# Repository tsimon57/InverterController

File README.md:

# InverterController
circuit to control MicroSolar inverter using remote cable socket
My vacation is your worst nightmare. Well, at least that is what the bumper sticker says – it’s referring to Burning Man. It’s well known that among the tens of thousands of people attending this arts festival in Nevada at the end of each Summer there are lots of high tech luminaries. I also have gone many times – not to say that I am a luminary. It’s a common tradition of so-called ‘burners’ to build complex projects to take with them that provide some of the comforts of home and more during the week of survival camping in the Black Rock Desert. Ad hoc showers, aluminum can recycling stations, elaborate cooking arrangements, alternative energy systems, coffee carts, colorful lighting setup, fire shooting vehicles, huge sound systems – pretty much anything you can think of and many you never even imagined – are brought out and assembled on the “playa.”

There is nothing for sale there – you must plan on bringing everything you need. There might be some sociable gifting, and people will probably help you out in a pinch, but start with the basics, like 2 gallons of water per person per day, and go from there. Notwithstanding, you can buy coffee and ice at what they call Center Camp. That’s it. Everything else is on you. The ice is for people’s coolers. And we are talking about 80,000 people camping in the desert heat. Of course, people bring RV’s (some consider that cheating) and others have generators and refrigerators (might also be cheating). I have relied on ice and coolers for many of my ten day stints out there. Needless to say, dealing with ice can be a major hassle. Getting very cold and heavy ice at Center Camp and bringing it back to your camp on foot or bicycle can be an ordeal. When it melts, it fills your cooler with slushy water that inevitably finds its way into your food. 

So I decided, what better project than to use solar power to run a small freezer to freeze blue ice packs? With a freezer working well enough, I can swap between two sets of blue ice packs each day. One set is getting deep frozen while the other set is keeping my Yeti cooler nice and cold. Last Summer, I started to assemble my system. It needed to be as compact as possible, weather proof, not easily damaged (either on the trip there or once set up), self-sustaining, reliable and reasonably priced. 

I ruled out an off the shelf solution because I wanted to better understand the realities of using solar power for something that we usually count on running off the mains. So, I started researching and shopping. The starting point for the whole system is the freezer. This established the requirements for everything else. The good news is that a 1.1 cubic foot freezer requires around 60 watts when running. This seemed like a totally doable load. 

Even though this is a solar powered system, a solar panel cannot deliver enough instantaneous power to turn over a motor. Therefore a battery would be needed. The first tests I performed were to start up the small 1.1 cubic foot Igloo freezer that I had bought as a factory second, on ebay for about $100. My first test using a 100 Watt combo inverter battery pack accomplished absolutely nothing. I then sought out a power meter to measure the wattage that was needed by the freezer. 

Plugging the unit into the wall with a watt meter showed load of well over 500 watts for up to 10 seconds at start up. This moved my requirement from a 100 watt inverter to a 600-1000 watt inverter. The other problem I was facing is that sealed lead acid batteries are not the best for driving high loads. I happen to own a large lithium power pack (battery and inverter combo) that can deliver 1000 watts which had no problem starting the freezer. But a stand-alone pure sine wave 1000 watt inverter can cost hundreds of dollars. I was sure that a 400 to 600 watt inverter could be made to work. Incidentally the large battery pack was not an option for the freezer because it can only handle 100 watts of solar power as input for charging. It would be a challenge to run the freezer and recharge its 1200 watt hours with the remaining 30-40 watts if needed. 

Because of the low weight and high current ratings of lithium batteries I started a search for an economical lithium battery pack. However, it had to be compatible with the common lead-acid chemistry charge controllers available on Amazon. I abandoned a couple of really heavy sealed lead acid batteries and bought one, then another, Dakota Lithium batteries - http://a.co/5Tty2HL
These have lots of surge power and are each rated at 120 watt hours. They are small, light and well priced.

I had a 700 watt modified sine wave inverter, but there were several things I did not like about it. And what is more, it still could not reliably start the freezer. This kicked off a deep dive into refrigerator motor design. Small cheap freezers, and probably more expensive ones, are a study in minimalist design. Those small back spheres that hold the compressor are cranked out by the millions. Inside is a motor with two coils, compressor piston, and a sealed oil lubrication and cooling system. Basically, the oil is lifted and sprayed around the interior by grooves on the motor shaft. They also have overheat protection. 

The electronics for starting the motor are on the outside, usually in a small plastic case pushed over the three pins that connect to the internals. In my case the power switch energizes the ‘run’ coil and the ‘start’ coil is initially connected but is disconnected when the current running through a small thermal switch causes it to open. Brute force, that assumes unlimited starting current and uses no intelligence. The worst-case scenario is when the compressor has been running and is then shut off and restarted again right away. The start coil is not engaged and the stalled motor draws hundreds of watts until the over-temperature inside the compressor triggers, which cannot be good for the motor. 

More sophisticated and better built appliances use inductors and/or capacitors in conjunction with relays and sensing circuits to deliver the starting coil current. This decreases the intial current draw substantially. I discovered an after-market so-called hard-start device designed for the standard refrigerator compressor motor. It is made by Supco - http://a.co/3ubL5wI It comes as a one pierce sealed unit that connects to pins that the plastic housing was connected to. While I do not have detailed numbers, it is clear that this $30 device solved most of the starting current problem I was facing. The freezer would start reliably and I was certain that an even lower powered inverter would work.

The 700 watt inverter was a modified sine wave inverter, which causes power loss in inductive loads like motors. I was looking build the most power efficient system,  and this seemed like something to improve. Also, a side effect of the modified sine waveform is that the motor runs hotter – due to the wasted power being transformed to heat. This particular inverter had a fan that would run even at low loads. It seemed unacceptable to have a 6-8 watt inverter load at idle. 10% of the system power would be going into the inverter at a minimum.

I wanted to set up a timer so that the freezer only ran during daylight hours. There were two choices. I could switch the AC power with a light timer, which are cheap and easy to setup. This has the disadvantage of requiring uninterrupted AC power to keep time properly. Another option is a DC timer, which has the advantage of not running the inverter at idle (3-5W) for the 18 hours the freezer is not running. If I have 240 watt hours of battery, you can see that ~40 watts hours adds up to a large percentage to lose every night. 

The system must be designed so the batteries have enough power reserve to start the motor in the morning, so current leakage overnight to run the idle inverter is unacceptable. A few low sun days could run this system into the ground. I found the perfect DC timer - http://a.co/c0d2RDR - that uses a battery to keep time, so it is immune to power outages. It is capable of switching large loads – the system can pull upwards of 10 Amps at startup. 

Back on Amazon I found a cheap pure sine inverter that looked like it would meet my needs. It is a MicroSolar 600W Pure Sine Inverter – http://a.co/cbzLs62 - for $89. Why not! It arrived and it worked great. There is no fan running in the inverter except under heavy loads – e.g. for start up, not at normal running currents. Soon though I discovered the Achilles heel of this system. 

I started out thinking that I could get by with 100 watts of solar panels. The cruel truth about solar panels is that they often output well below their rated power. The worst offenders are the flexible panels – like the ones I wanted to use because they weigh less, are harder to damage and take up less room in transit. After many experiments, I opted for 4 panels each rated at 120 watts for $120 each. https://www.solarblvd.com/product_info.php?products_id=3082 They can output close to 80-90 watts each in full overhead sun. So, the whole array can output an impressive 350 watts peak power. I could probably pare down to fewer panels, but the extra generation capability means faster battery recovery and more tolerance for cloudy days. It also means I can charge other loads and run the freezer at the same time. Think batteries for lighting, etc. 

The most important link in the system is the charge controller. This takes the raw DC power from the solar panel array and feeds it to the 12V batteries. The panels each output between 12 and 25 volts. If they are wired in series this typically means there is 80V DC feeding into the controller. Solar panels are very fussy about the IV curve they produce. For any given lighting situation and load there is an optimal IV point which has the panel producing the maximum power. 

There are two kinds of charge controllers: PWM and MPPT. PWM is pulse width modulation, and MPPT is maximum power point tracking. You want MPPT. PWM just toggles the current to battery at varying duty cycles to charge the battery. PWM is not very efficient and it does not allow the panels to produce the maximum power. MPPT uses a microprocessor that walks the charging voltage up and monitors the current to calculate the change in total power. MPPT will bring the voltage up to the point where the maximum power is produced by the panel. Then there is circuitry that produces the desired output voltage for the batteries. This extra circuitry is more expensive, but the efficiencies are often in the high 90% range. There is a substantial price boost for MPPT, but for the system efficiency requirements it seemed worth it. I chose a MPPT unit made by Renogy - http://a.co/1GFnZSI The alternative was buying more batteries or solar panels. 

The inverter draws so much power at the freezer startup it exceeded the “load” terminal rating on the charge controller, so the inverter load just gets connected to the battery terminals. In essence the charge controller thinks it is charging the batteries when the load is powered. The batteries are acting as a ballast. The one requirement for the charge controller I purchased is that it must always have 12V from the battery to run. If the battery runs down, it cannot recharge it, even if there is power coming from the solar panels. This is a reasonable restriction for a lead acid battery, but I am using lithium batteries with a low voltage cut out that is above the inverter low voltage cut out. The inverter will run the lithium batteries until they shut down. At which point the system needs a “jump start”. 

Once it became clear how serious this problem was, I realized I needed to monitor the voltage. Not only did it need to shut off above the minimum discharge level, to ensure the controller always had power, it needed to wait until the batteries had recovered significant charge before re-engaging the inverter and freezer load. 

Another major problem was that because the on-off control for the inverter was designed using a momentary switch, the unit would need manual attention every time the DC power to it was restored. There was no way to leave the unit ‘on’ so it would power on after DC voltage was applied when the timer turned on in the morning.

However, my choice of inverter turned out to be fortuitous. It came with a wired remote on-off switch; but it was even better because it also featured ‘run’ and ‘fault’ indicator lights. This combination meant that I could design a circuit that plugged in to the socket for the remote switch module and use a microcontroller to actively manage the system behavior. I could design a circuit to monitor the battery voltage and turn the inverter on and off as needed to keep the battery levels exactly where I wanted them. I could probably even eliminate the timer, but there is some advantage to shutting everything down well after dark.

I have extensive experience building projects with Arduinos – small easy to program and use microcontroller circuits. It’s easy to buy these small prebuilt boards that can be programmed over USB from a PC. They come with an on-board voltage regulator chip that operates with 12 to 15 volts, so the battery for the solar system can provide the power. Internally Arduinos operate on 5V, which is the voltage regulator output. The Arduino comes with digital I/O pins and analog input pins connected to the internal ADC. There is also support for SPI and I2C for connecting external devices and peripherals. 

I needed to bring a 12V line high or low to create the effect of pressing the button on the inverter remote control, and also read three analog signals – run, fault and the battery line voltage. The ADC on the Arduino only supports 0-5V, so a voltage divider is required. This can be built with a 1M ohm and 100K ohm resistor. I reverse engineered the signal lines on the remote cable. It has 4 wires. One is always ‘high’ and the run, fault and start-button all use it as the return. When the run or fault light is on, their voltage goes low, creating a current flow through the LED. The start button is pulled high when the button is pushed, because then it is connected to the high signal.

To control the start button I designed a simple circuit with an NFET and a pull up resistor on the drain side. With this the drain floats high until the NFET is closed by a 5V gate voltage. Then it is pulled down to ground. I own a milling machine, called the OtherMill, that makes it easy to produce my own custom printed circuit boards. I created a circuit in EagleCAD and then designed a PCB layout that can be milled on the OtherMill. It has pads for piggy back connections to the Arduino board I chose to use – Arduino Nano. These cost about $5 each and can be purchased on Amazon or Ebay.

Next came the software development. The Arduino comes with a free development environment. There are many libraries that make reading the analog signals and controlling the digital I/O’s easy. I also found coding example for the voltage divider. With some trial and error, I was able to write a program that would start up the inverter when power was applied and then monitor the status of the inverter and the battery voltage. I set a low voltage cutoff of 12 volts and have it wait until the battery voltage reaches 13.4 to restart, ensuring that the batteries have a reasonable level of charge before resuming operation.

My circuit also needed to avoid the death spiral of turning the unit back on after it had just stopped running. As is mentioned above if the freezer attempts to restart after just being turned off, the stalled motor draws heavy current and overheats. I added code to check to see if there is a fault and then ensures that there is a two minute delay before attempting a restart. 

Having the automatic control was nice, but running without any external display or indicators was difficult during software debug. There is a capability to add println() debugging when the Arduino is plugged into a PC, but I wanted to know the system status when the circuit is running in the field and not attached to a PC. This was solved with a 4 line LCD display that is compatible with the Arduino and costs about $15. I added code to display the battery voltage, system status and whether a fault had occurred on the inverter. The LCD display runs on the I2C bus and required a slight redesign of the PCB to add a 4 pin connector.

The last piece of this project is to add a small box for the custom electronics. I already purchased a larger waterproof case to hold the all the electronics: inverter, charge controller, timer, custom circuit and batteries. I opted to design a small circuit box using 3D CAD software and use a 3D printer to fabricate it. My favorite 3D modeling software is Onshape. A free account allows ‘public’ designs and a limited number of ‘private’ designs. The user interface is all web based, but don’t be fooled. This is a high-end tool, that uses cloud compute resources to provide sophisticated functionality. I own a FlashForge Creator Pro 3D printer and printed the box first in PLA and then in ABS. Hopefully the finished design for the box will hold up in the withering heat at Burning Man. 

Everything fits into the waterproof case and there is a water resistant flap for inserting cables from the solar array and the inverter. There is an additional load line to recharge another external 12V battery pack for other uses. There will be some clean up and rewiring to make thing more tidy. However, the whole system is up and running in my back yard. I also ran a series of tests to see how cold the cooler can stay with swapping cold packs every evening. I am looking forward to testing everything out in the Spring on a relaxing car camping trip. It will be nice to have cold beer without having to make ice runs.

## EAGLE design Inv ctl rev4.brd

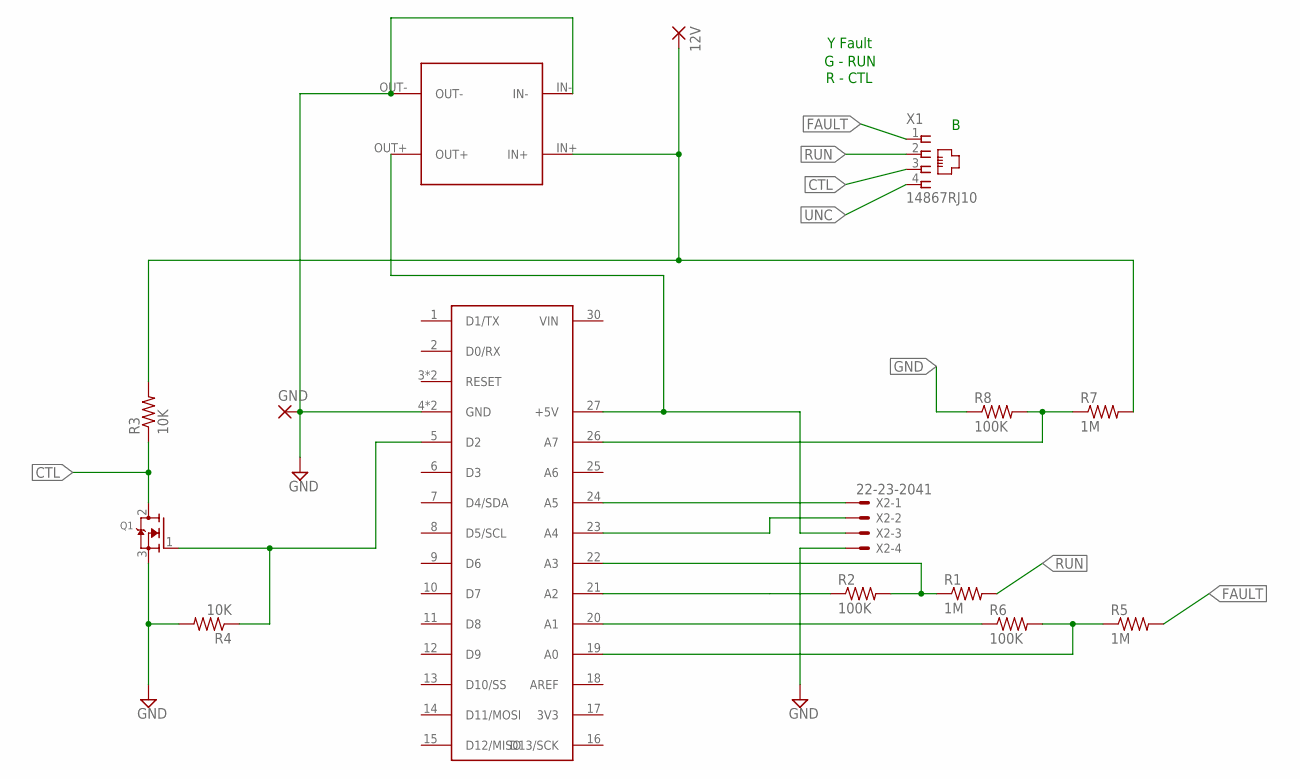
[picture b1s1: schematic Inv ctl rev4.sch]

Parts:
12V: 3,81/1,4
GND: 3,81/1,4
Q1: MOSFET-N; TO252
R1, R5, R7: 1M; R1206
R2, R6, R8: 100K; R1206
R3, R4: 10K; R0805
U$1: ARDUINO_NANO
U$2: LM2956_MODULE; LM2596_MODULE
X1: 14867RJ10; RJ10
X2: 22-23-2041

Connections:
12V: 12V.1, R3.2, R7.2, U$2.IN+
CTL: Q1.2 (D), R3.1, X1.3
FAULT: R5.2, X1.1
GND: GND.1, Q1.3 (S), R4.2, R8.1, U$1.4 (GND), U$1.29 (GND), U$2.IN-, U$2.OUT-, X2.4
LINEVOLTAGE: R7.1, R8.2, U$1.26 (A7)
unnamed: Q1.1 (G), R4.1, U$1.5 (D2)
unnamed: U$1.27 (+5V), U$2.OUT+, X2.3
unnamed: R2.1, U$1.21 (A2)
unnamed: R6.1, U$1.20 (A1)
unnamed: R5.1, R6.2, U$1.19 (A0)
RUN: R1.2, X1.2
RUNMODE: R1.1, R2.2, U$1.22 (A3)
SCL: U$1.24 (A5), X2.1
SDA: U$1.23 (A4), X2.2
UNC: X1.4

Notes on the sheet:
Y Fault
G - RUN
R - CTL

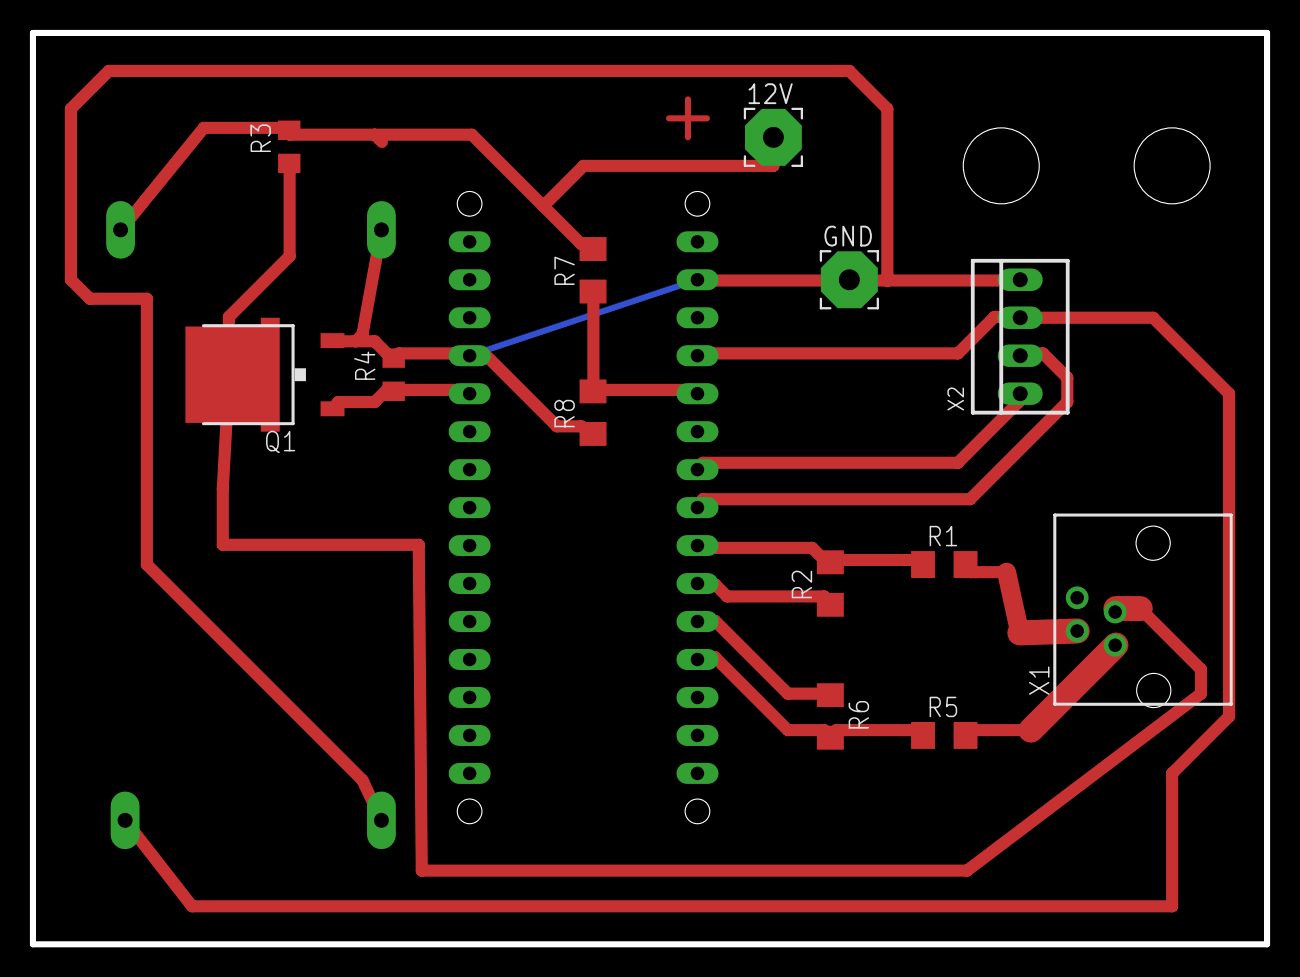
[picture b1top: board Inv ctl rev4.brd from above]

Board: 2 copper layers, 82.6 x 61.0 mm, 15 parts (1 on the bottom side), 14 nets.

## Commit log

2016-12-18 Initial upload of project files
2016-12-18 Add copy of article summarizing project development
2016-12-18 STEP Files for case
2017-05-19 Updated code for the rev 3 board
2017-05-23 Updated board and schematic to use Buck converter module from ebay instead of ob-board LDO
2017-05-23 specs for ebay buck converter
2017-05-23 Case for Rev 4 board
    New case that just fits the Rev 4 board with the piggy back buck converter
